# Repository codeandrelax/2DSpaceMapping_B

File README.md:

# AUTONOMNO VOZILO - PROJEKTNI ZADATAK
Ovaj repozitorijum sadži dokumentaciju potrebnu za izradu projektnog zadataka iz predmeta Računarska elektronika/Mikrokontrolerski sistemi na Elektrotehničkom fakultetu u Banjoj Luci. Na projekatu rade tri studenta na četvrtoj godini. Cilj projekta jeste implementacija sistema za autonomnu vožnju koji može bezbijedno i efikasno upravljati vozilom. Sistem se nadograđuje na [Joy-car](https://joy-it.net/en/products/mb-joy-car) sa specificiranim zahtjevima.

# Specifikacija projektnog zadataka 
### Upravljačka PCB ploča
Potrebno je realizovati PCB pločicu koja ispunjava sljedeće zahtjeve: 
* PCB pločica može biti maksimalno dvoslojna.
* Koristi se SMD tip komponenti
* Minimalna širina veze prilikom rutiranja iznosi 0.254 mm, a minimalno rastojanje između komponenata 0.1 mm.
* Korišćenje mikrokontrolera (MCU) tipa PIC24FJ64GAxx za upravljanje i kontrolu sistema.
* Podrška za komunikaciju putem UART, SPI i I2C interfejsa za povezivanje različitih komponenti.
* Integracija Wi-Fi modula za bežičnu komunikaciju i daljinsko upravljanje.
* Upotreba već postojećeg baterijskog napajanja.
* Budzet za kupovinu komponenata od 20 do 30 dolara.

### IR Distance Click senzor
* Kretanje vozila na osnovu očitavanja senzora.
* Implementacija 2D mapiranja prostora oko vozila korišćenjem senzora.

## Aplikacija
* Razvoj aplikacije za prikazivanje okoline oko vozila.
* Mogućnost pokretanja i zaustavljanja vozila putem aplikacije, 2D prikaz reljefa.

## Projektovanje štampane ploče
* Šema 

* Layout  

* 3D model  

## Realizacija algoritma kretanja vozila

Potpuno integrisano samoupravljajuće vozilo Joy Car funkcioniše na taj način da se IR click senzor vozila najprije centrira tako da skenira prostor ispred sebe i vozilo se počinje kretati ravno, to je jedan od pet mogućih pravaca kretanja vozila. Nakon što vozilo prilikom kretanja naiđe na prepreku koja se nalazi na udaljenosti od 15cm, zaustavlja se i skenira se prostor oko vozila, tako što se okreće IR Distance Click senzor koji je postavljen na servo motoru koji se okreće za ugao od 45 stepeni u desnu stranu, odnosno lijevu. Nakon što na osnovu vrijednosti napona koju senzor generiše odredimo u kojem smjeru se prepreka nalazi najdalje, vozilo se počinje kretati u tom pravcu. Ukoliko su vrijednosti očitavanja senzora veće, tada se prepreka nalazi bliže vozilu i obratno. U slučaju da se prepreka nalazi jako blizu tada autić zbog širine točkova nije u mogućnosti da nesmetano skrene u željenom pravcu pa postoji i dodatni smijer kretanja, unazad. Tada autić najprije vozi nekoliko centimetara unazad, a zatim skrene u pravcu za koji je utvrdio da je najpovoljniji.  

Na slici ispod je prikazan primjer simulacije kretanja autića u lavirintu. 

Na gifu ispod prikazano je kretanje autića kroz lavirint:

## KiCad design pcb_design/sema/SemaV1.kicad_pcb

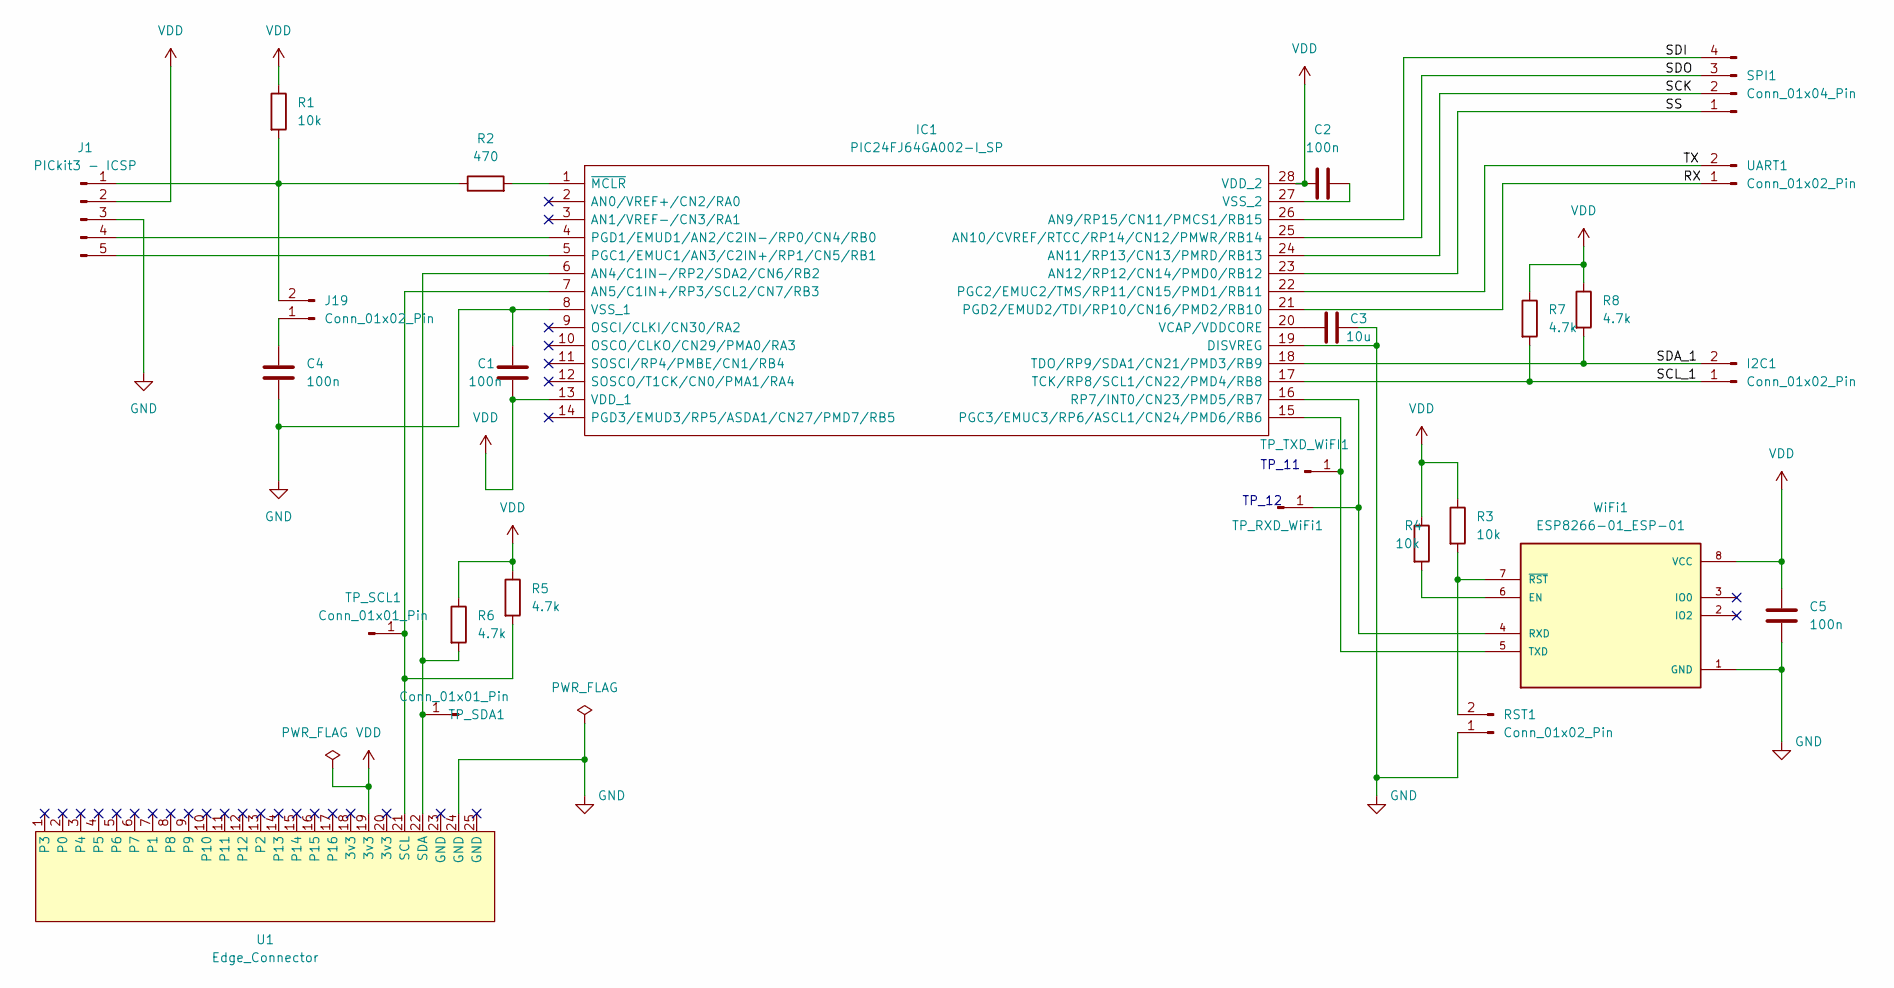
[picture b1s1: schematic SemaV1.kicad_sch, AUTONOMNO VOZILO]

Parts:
C1, C2, C4, C5: 100n; C1812
C3: 10u; C1812
I2C1: Conn_01x02_Pin; HDRV2W66P0X254_1X2_508X254X874P
IC1: PIC24FJ64GA002-I_SP; DIP794W56P254L3486H508Q28N; Mouser Part Number 579-PIC24FJ64GA002SP
J1: PICkit3 - ICSP; HDRV5W67P0X254_1X5_1229X234X821P
J19: Conn_01x02_Pin; HDRV2W66P0X254_1X2_508X254X874P
R1, R3, R4: 10k; RESC6432X120N
R2: 470; RESC6332X65N
R5, R6, R7, R8: 4.7k; RESC6432X65N
RST1: Conn_01x02_Pin; HDRV2W66P0X254_1X2_508X254X874P
SPI1: Conn_01x04_Pin; HDRV4W64P0X254_1X4_1016X254X889P
TP_RXD_WiFi1: Conn_01x01_Pin; SolderWire-0.1sqmm_1x01_D0.4mm_OD1mm
TP_SCL1: Conn_01x01_Pin; SolderWire-0.1sqmm_1x01_D0.4mm_OD1mm
TP_SDA1: Conn_01x01_Pin; SolderWire-0.1sqmm_1x01_D0.4mm_OD1mm
TP_TXD_WiFI1: Conn_01x01_Pin; SolderWire-0.1sqmm_1x01_D0.4mm_OD1mm
U1: Edge_Connector
UART1: Conn_01x02_Pin; HDRV2W66P0X254_1X2_508X254X874P
WiFi1: ESP8266-01_ESP-01; XCVR_ESP8266-01_ESP-01; PARTREV V1.2

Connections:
/RX: IC1.21 (PGD2/EMUD2/TDI/RP10/CN16/PMD2/RB10), UART1.1
/SCK: IC1.24 (AN11/RP13/CN13/PMRD/RB13), SPI1.2
/SCL_1: I2C1.1, IC1.17 (TCK/RP8/SCL1/CN22/PMD4/RB8), R7.2
/SDA_1: I2C1.2, IC1.18 (TDO/RP9/SDA1/CN21/PMD3/RB9), R8.2
/SDI: IC1.26 (AN9/RP15/CN11/PMCS1/RB15), SPI1.4
/SDO: IC1.25 (AN10/CVREF/RTCC/RP14/CN12/PMWR/RB14), SPI1.3
/SS: IC1.23 (AN12/RP12/CN14/PMD0/RB12), SPI1.1
/TX: IC1.22 (PGC2/EMUC2/TMS/RP11/CN15/PMD1/RB11), UART1.2
GND: C1.1, C3.2, C4.2, C5.1, IC1.8 (VSS_1), IC1.19 (DISVREG), J1.3, RST1.1, U1.24 (GND), WiFi1.1 (GND)
unnamed: IC1.6 (AN4/C1IN-/RP2/SDA2/CN6/RB2), R6.2, TP_SDA1.1, U1.22 (SDA)
unnamed: IC1.7 (AN5/C1IN+/RP3/SCL2/CN7/RB3), R5.2, TP_SCL1.1, U1.21 (SCL)
unnamed: IC1.5 (PGC1/EMUC1/AN3/C2IN+/RP1/CN5/RB1), J1.5
unnamed: IC1.15 (PGC3/EMUC3/RP6/ASCL1/CN24/PMD6/RB6), TP_TXD_WiFI1.1, WiFi1.5 (TXD)
unnamed: IC1.4 (PGD1/EMUD1/AN2/C2IN-/RP0/CN4/RB0), J1.4
unnamed: IC1.16 (RP7/INT0/CN23/PMD5/RB7), TP_RXD_WiFi1.1, WiFi1.4 (RXD)
unnamed: C3.1, IC1.20 (VCAP/VDDCORE)
unnamed: C2.2, IC1.27 (VSS_2)
unnamed: IC1.1 (~MCLR), R2.2
unnamed: J1.1, J19.2, R1.2, R2.1
unnamed: C4.1, J19.1
unnamed: R3.2, RST1.2, WiFi1.7 (~RST)
unnamed: R4.2, WiFi1.6 (EN)
VDD: C1.2, C2.1, C5.2, IC1.13 (VDD_1), IC1.28 (VDD_2), J1.2, R1.1, R3.1, R4.1, R5.1, R6.1, R7.1, R8.1, U1.19 (3v3), WiFi1.8 (VCC)

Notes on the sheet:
TP_12
TP_11

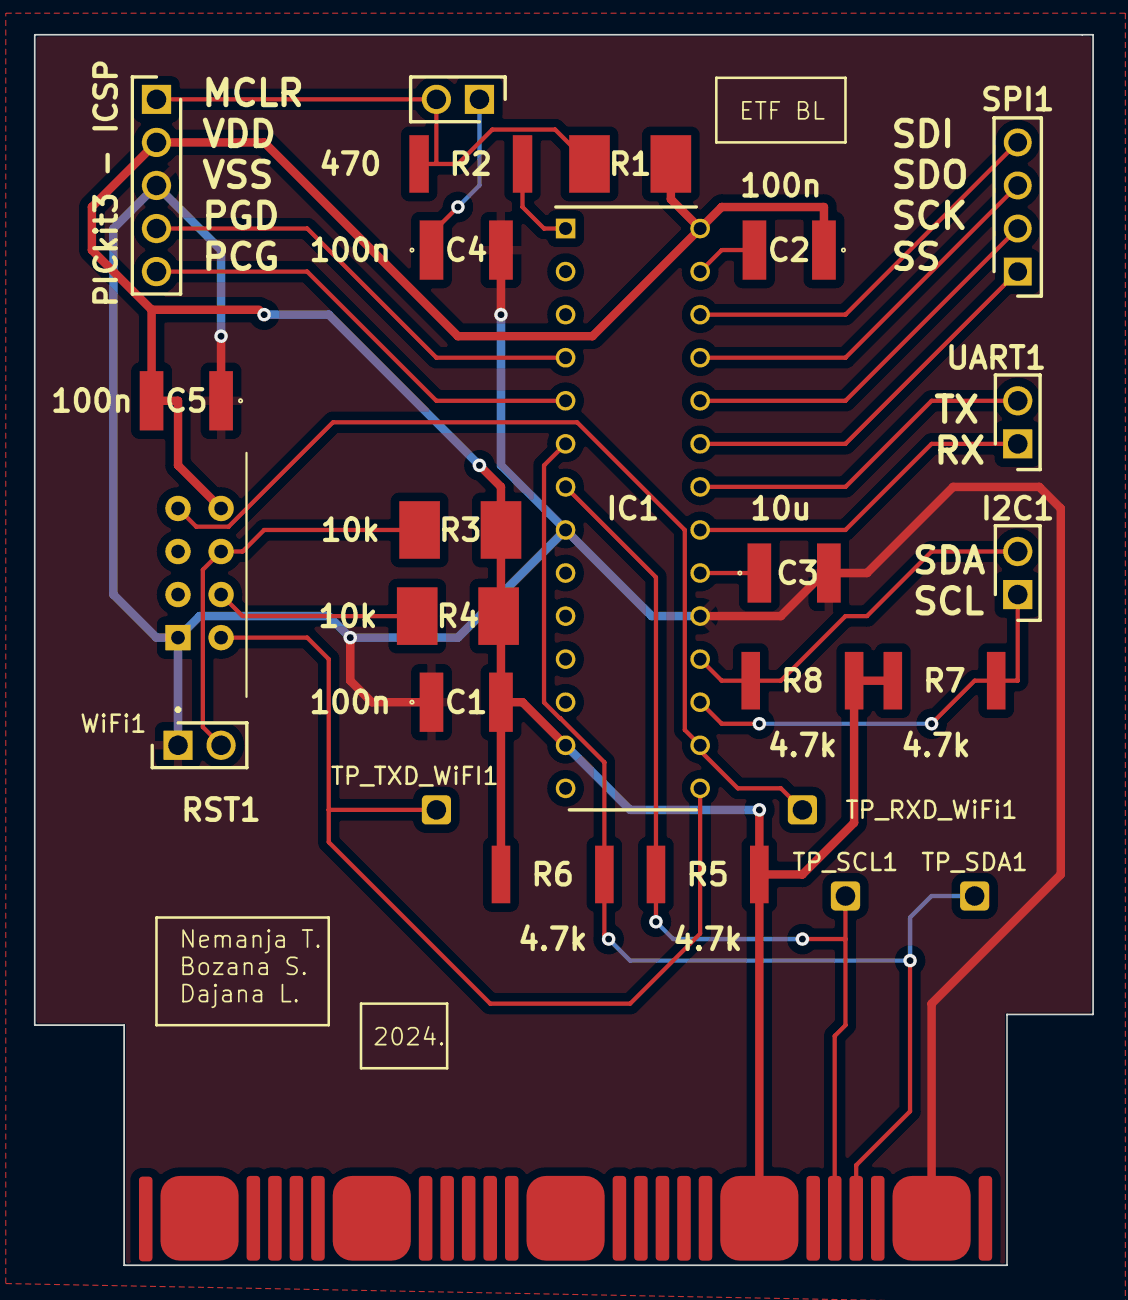
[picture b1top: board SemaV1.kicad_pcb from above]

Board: 2 copper layers, 62.4 x 72.6 mm, 26 parts (0 on the bottom side), 23 nets.

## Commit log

2024-01-28 -Dodavanje osnovne šeme sa mikrokontrolerom i minimalnom konfiguracijom
    - Dodavanje dokumentacije u vezi dodavanja osnovne šeme
2024-01-30 - Azuriranje seme
    - Dodavanje modula za WiFi
2024-01-30 -Dodavanje bloka za programiranje na šemu
    - Podrazumijeva dodavanje konektora za pinove i spajanja sa mikrokontrolerom
2024-01-30 Proširivanje dokumentacije
    - Dodavanje dokumentacije o dodavanju wifi modula
    - Dodavanje dokumentacije o dodavanju bloka za programiranje
2024-01-30 -Dodavanje modela projektovanog edge connector-a
    -Dodavanje simbola i dodavanje footprint-a
2024-01-31 Azuriranje seme
    - Dodavanje edge connector-a na semu, spajanje I2C pinova sa mikrokontrolera i spajanje napajanja i mase
    - Dodavanje ostalih konektora za eksterne interfejse (I2C, UART, SPI)
2024-01-31 Dodavanje dokumentacije projektovanja šeme, nakon dodavanja dijelo o napajanju, edge connector-u i eksternim interfejsima
2024-01-31 -Dodavanje testnih tacaka na semu, za potrebe kasnijeg testiranja
    - Izmjena imena foldera iz semav1 u sema
2024-02-01 Dodavanje završnog dizajna pločice
    Rutiranje komponenata
2024-02-07 Dodavanje pcb fajla sa rutiranim komponentama
    Sitne izmjene sa semi
2024-02-07 Dodavanja .csv fajla sa odabirom komponenata
2024-02-08 Dodavanje pdf dokumenta sa kompletnom šemom
    Dodavanje pdf dokumenta sa layout-om komponenata i 3d modelom
2024-02-25 Issue #25: Izmjena fajl hijerarhije na repozitorijum i sredjivanje dokumentacije
    - Dodavanje docs podfoldera za smjestanje dokumenteacije i izvjestaja
    - Sredjivanje podfoldera pcb_design. Izmjenjen naziv foldera sema u kicad_schematic_pcb jer se unutra nalaze kicad fajlovi projekta
    - Dodavanje .gitignore fajla sa ignorisanje nepotrebnih kicad fajlova
2024-02-26 Issue #22 : Rutiranje PCB-a
    - Izmjene footprint-a svih otpornika
    - Izmjene rutiranja komponenata u skladu sa primjedbama
2024-02-26 Issue #25: Izmjena fajl hijerarhije na repozitorijum i sredjivanje dokumentacije
    - Izmjena layout_3d_model.pdf fajla zbog izmjena u rutiranju pcb-a
2024-03-30 Issue #36: Testiranje stampane plocice nakon lemljenja komponenata
    -Testiranje spustanja programa na mikrokontroler
    -Dodavanje C programa za mikroC kompajler kojim se na pinu RB15 pali i gasi led dioda svake sekunde
2024-03-30 Issue #34: Simuliranje mapiranja prostora oko vozila
    -Python aplikacija koja simulira mapiranje prostora oko senzora koristeci pygame modul iz python-a
    -Dodavanje fajla sensor.py, koji u sebi sadrzi klasu Sensor i u kojoj se simulira rad senzora
    -Dodavanje fajla main.py koji u sebi sadrzi glavni program i ukljucuje senzor te iscrtava prostor oko njega
2024-03-30 Issue #38: Testiranje IR Distance Click komponente
    -Dodavanje C fajla za mikroC kompajler
    -Program konfigurise jedan port mikrokontrolera kao analogni ulazni pin na koji se dovodi izlaz senzora
    -Konfigurise AD konvertor za konverziju podataka sa analognog pina
    -Na osnovu vrijednosti sa senzora i postavljenog praga, odlucuje da li se ukljucuje ili iskljucuje dioda povezana na jedan izlazni digitalni pin
2024-04-08 Issue #42 : Testiranje i pokretanje servo motora za senzor
2024-04-15 Issue #43: Konfiguracija I2C-a za pokretanje motora na tockovima
    - Dodavanje koda za testiranje pokretanja motora tockova na vozilu
    - Dodan je testni C kod za mikroC kompajler koji konfigurise vozilo tako da se krece naprijed
2024-04-18 Issue #44: Konfiguracija WiFi modula
    - Dodavanje C fajla za testiranje WiFi modula
2024-04-23 Issue #46 : Kreiranje algortima kretanja vozila na osnovu ocitavanja senzora
    - Dodavanje prve verzije koda
2024-04-23 Issue #46 : Kreiranje algortima kretanja vozila na osnovu ocitavanja senzora
    - Modifikacija organizacije direktorijuma za dodavanje novih potrebnih fajlova
2024-04-24 Issue #48: Integrisanje rada servo motora i rada senzora Dodan C fajl
2024-04-25 Issue #46: Kreiranje algoritma kretanja vozila na osnovu očitavanja senzora - Dodavanje testnog .c programa u kojem se integrise rad senzora i servo motora sa točkovima
2024-05-08 Issue #44: Konfiguracija WiFi modula
    -Dodavanje izmjenjenog koda za testiranje rada wifi modula
    -Izmjena se odnosi na koristenje UART interapta umjesto poling principa
    -Druga izmjena je brisanje flega koji kada je setovan oznacava da je UART fifo bafer pun, svaki put kada se desi UART Error interapt
2024-05-09 Issue #46: Kreiranje algoritma kretanja vozila na osnovu ocitavajna senzora
    - Razdvajanje programa na module radi bolje citljivosti
    - Program podijeljen u modul koji se odnosi na sensor: servo_sensor.c(.h) i koji se odnosi na upravljanje vozilom car_drive.c(.h)
    - Dodavanje Doxygen komentara radi generisanja dokumentacije
2024-05-10 Issue #46: Kreiranje algoritma kretanja vozila na osnovu ocitavajna senzora
    - Unaprijedjenje algoritma kretanja
    - Mogucnost kretanja unazad kada se vozilo nadje u situaciji kada ne moze da ide ni u jednom od mogucih pet pravaca
    - Bolje skeniranje prostora nakon zaustavljanja
    - Dodavanje koementara za Doxygen dokumentaciju
2024-05-10 Issue #46: Kreiranje algoritma kretanja vozila na osnovu ocitavajna senzora
    - Uklanjanje starog nepotrebnog main_program.c fajla
2024-05-13 Issue #47: Sredjivanje wiki dokumentacije i dokumentacija koda
    - Sredjivanje, dodavanje i ispravljanje komentara u kodu
    - Promjena imena fajla sa main funckijom iz modular_drive_car.c u main_program.c
2024-05-14 Issue #47: Sredjivanje wiki dokumentacije i dokumentacija koda
    - Dodavanje index.html fajla sa generisanom Doxygen dokumentacijom za kod
2024-05-14 Issue #47: Sredjivanje wiki dokumentacije i dokumentacija koda
    - Dodavanje Doxygen dokumentacija za /integration/servo_sensor.c fajl, kao i dodavanje index.html fajla za generisanom dokumentacijom
2024-05-14 Issue #47: Sredjivanje wiki dokumentacije i dokumentacija koda
    - Dodavanje Doxygen dokumentacija za /integration/drive_servo_sensor.c fajl, kao i dodavanje index.html sa generisanom dokumentacijom
2024-05-14 Issue #47: Sredjivanje wiki dokumentacije i dokumentacija koda
    - Prebacivanje generisane html dokuementacije u folder /docs
2024-05-14 Issue #47: Sredjivanje wiki dokumentacije i dokumentacija koda
    - Dodavanje dokumentacije za testing/ir_distance_click
2024-05-14 Issue #47: Sredjivanje wiki dokumentacije i dokumentacija koda
    - Dodavanje doxygen generisane dokumentacije za testing/led_blinking
2024-05-14 Issue #47: Sredjivanje wiki dokumentacije i dokumentacija koda
    - Dodavanje doxygen generisane dokumentacije za testing/servo_sensor
2024-05-14 Issue #47: Sredjivanje wiki dokumentacije i dokumentacija koda
    - Dodavanje doxygen generisane dokumentacije za testing/wheels_i2c
2024-05-14 Issue #47: Sredjivanje wiki dokumentacije i dokumentacija koda
    - Dodavanje doxygen generisane dokumentacije za testing/wifi_module
